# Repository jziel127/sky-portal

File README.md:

# Sky Portal — Automated Circadian Lighting & Clock

A personal engineering project that adds automation and a companion display to a [Chroma Sky Portal 2.1](https://getchroma.co/) circadian light — without modifying the light itself.

## What it does

- **Automates the Sky Portal's settings** (brightness/"Photon" and color temperature/"Red-White Ratio") throughout the day, driven by real solar and weather data rather than a physical light sensor. Small external servos physically turn the light's existing knobs, so the device itself is never opened or altered.
- **Auto power on/off** via a third, higher-torque servo that physically flips the unit's power switch.
- **A companion 16x16 LED matrix** running [WLED](https://kno.wled.ge/) on an ESP32 shows a clock, the date, and the current outdoor weather (with a simple animated icon and temperature), cycling automatically.

## How it works (high level)

```
Windows mini PC (central brain)
   │  pulls solar elevation + cloud cover from OpenWeatherMap
   │  computes a "circadian phase" for the day
   │
   ├── USB Serial ──► Arduino Pro Mini ──► 3 servos (Photon, Color Ratio, Power)
   │
   └── HTTP/MQTT ──► ESP32 (WLED) ──► 16x16 LED matrix (clock + weather display)
```

## Hardware

- Chroma Sky Portal 2.1 (the light being automated)
- Windows mini PC (GMK NucBox5) — control logic, API calls
- Arduino Pro Mini + FTDI adapter — servo control
- 2x SG90 micro servos + 1x MG996R servo
- ESP32 + WS2812B 16x16 LED matrix, running WLED
- Custom 3D-printed enclosure housing the electronics, attached to the light's stand

## Status

Actively in progress — the LED matrix clock is fully built and running; the servo/knob automation is the current phase of work.

## Why this project exists

Built as a personal engineering/robotics project to combine embedded systems, API integration, and mechanical design into something used every day — not a commercial product, and not affiliated with Chroma.

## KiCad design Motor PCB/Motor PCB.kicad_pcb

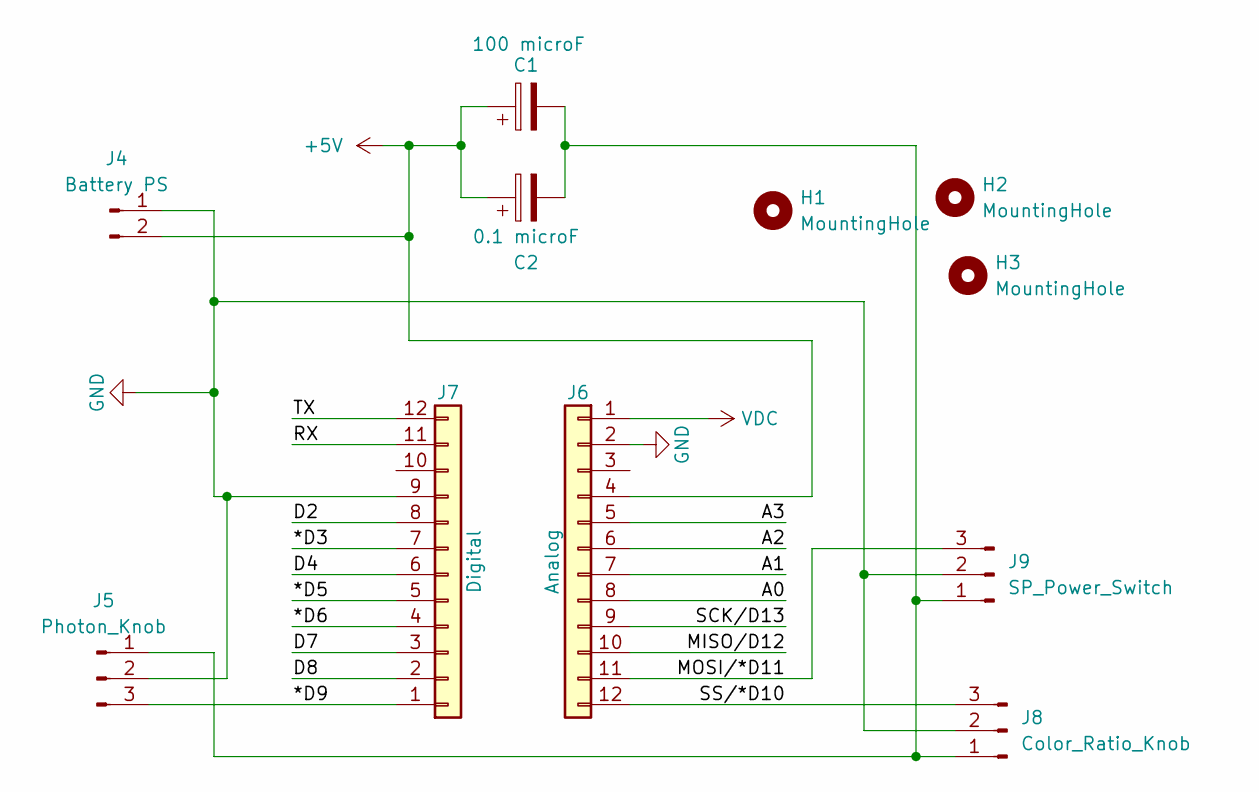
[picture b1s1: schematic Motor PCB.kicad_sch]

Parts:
C1: 100 microF; CP_Radial_D6.3mm_P2.50mm
C2: 0.1 microF; C_Disc_D5.0mm_W2.5mm_P2.50mm
H1, H2, H3: MountingHole; MountingHole_2.2mm_M2
J4: Battery PS; PinHeader_1x02_P2.54mm_Vertical
J5: Photon_Knob; PinHeader_1x03_P2.54mm_Vertical
J6: Analog; PinHeader_1x12_P2.54mm_Vertical
J7: Digital; PinHeader_1x12_P2.54mm_Vertical
J8: Color_Ratio_Knob; PinHeader_1x03_P2.54mm_Vertical
J9: SP_Power_Switch; PinHeader_1x03_P2.54mm_Vertical

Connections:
+5V: C1.1, C2.1, J4.2, J6.4
/*D3: J7.7
/*D5: J7.5
/*D6: J7.4
/*D9: J5.3, J7.1
/A0: J6.8
/A1: J6.7
/A2: J6.6
/A3: J6.5
/D2: J7.8
/D4: J7.6
/D7: J7.3
/D8: J7.2
/MISO/D12: J6.10
/MOSI/*D11: J6.11, J9.3
/RX: J7.11
/SCK/D13: J6.9
/SS/*D10: J6.12, J8.3
/TX: J7.12
GND: J4.1, J5.2, J6.2, J7.9, J8.2, J9.2
unnamed: C1.2, C2.2, J5.1, J8.1, J9.1
VDC: J6.1

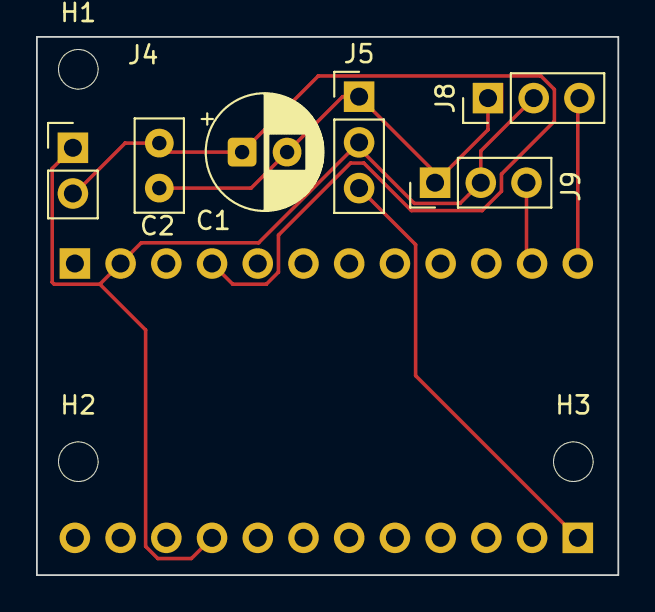
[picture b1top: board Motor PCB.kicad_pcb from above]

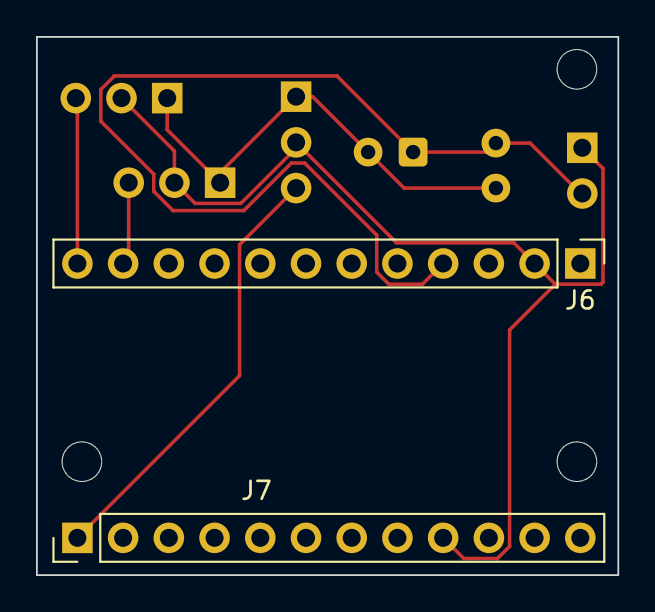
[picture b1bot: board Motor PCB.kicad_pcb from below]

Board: 2 copper layers, 32.3 x 29.9 mm, 11 parts (2 on the bottom side), 6 nets.
